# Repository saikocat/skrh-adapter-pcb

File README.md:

# skrh-adapter-pcb
Alps SKRH Switch Adapter PCB

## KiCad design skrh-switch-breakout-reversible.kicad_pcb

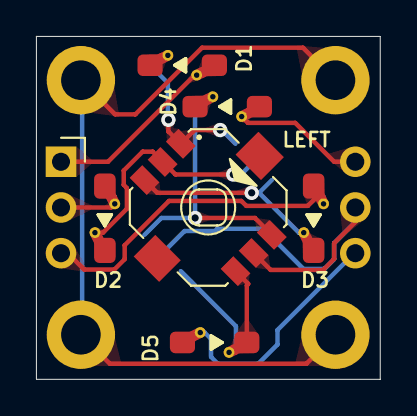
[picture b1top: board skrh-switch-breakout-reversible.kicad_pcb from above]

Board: 2 copper layers, 19.1 x 19.1 mm, 11 parts (0 on the bottom side), 12 nets.

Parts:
D1, D2, D3, D4, D5: 1N4148; Diode_D_SOD-123_Silkless_Reversible
H1, H2, H3, H4: Hole; MountingHole_2.2mm_M2_Pad_3.8mm
S1: SW_MultiDirectional_4DCP_SKRHACE010; SW_MultiDirectional_4DCP_SKRHACE010_SMD_7.5x7.5mm_DualSide
S2: Source; SW_MX_1u_PCB_SKRHAdapter

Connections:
A_SRC: D1.2 (A), S2.1 (A)
A_UP: D1.1 (K), S1.1 (A)
B_RIGHT: D4.1 (K), S1.4 (B)
B_SRC: D4.2 (A), S2.4 (B)
COMMON: S1.5 (COM), S2.5 (COM)
C_LEFT: D3.1 (K), S1.3 (C)
C_SRC: D3.2 (A), S2.3 (C)
D_DOWN: D5.1 (K), S1.6 (D)
D_SRC: D5.2 (A), S2.6 (D)
GND: H1.1, H2.1, H3.1, H4.1
PUSH: D2.1 (K), S1.2 (CENTER)
PUSH_SRC: D2.2 (A), S2.2 (CENTER)

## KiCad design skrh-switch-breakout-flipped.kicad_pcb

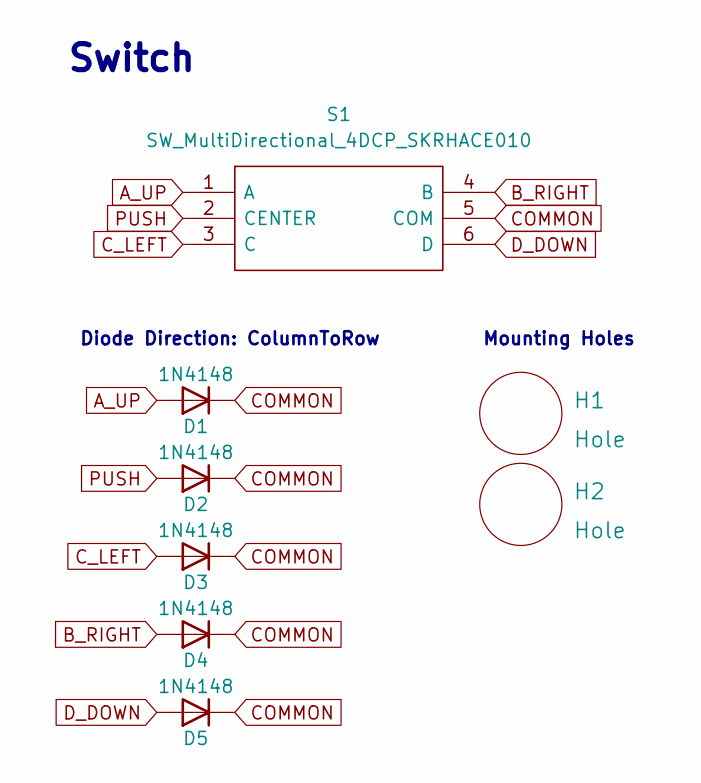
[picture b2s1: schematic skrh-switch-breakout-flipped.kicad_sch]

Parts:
D1, D2, D3, D4, D5: 1N4148; Diode_D_SOD-123_Silkless_Reversible
H1, H2: Hole; MountingHole_2.3mm_M2_Threaded_ISO14580_Pad
S1: SW_MultiDirectional_4DCP_SKRHACE010; SW_MultiDirectional_4DCP_SKRHACE010_SMD_7.5x7.5mm_Breakout_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; Manufacturer_Part_Number SKRHACE010; Mouser Part Number 688-SKRHAC

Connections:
A_UP: D1.2 (A), S1.1 (A)
B_RIGHT: D4.2 (A), S1.4 (B)
COMMON: D1.1 (K), D2.1 (K), D3.1 (K), D4.1 (K), D5.1 (K), S1.5 (COM)
C_LEFT: D3.2 (A), S1.3 (C)
D_DOWN: D5.2 (A), S1.6 (D)
PUSH: D2.2 (A), S1.2 (CENTER)

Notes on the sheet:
Mounting Holes
Switch
Diode Direction: ColumnToRow

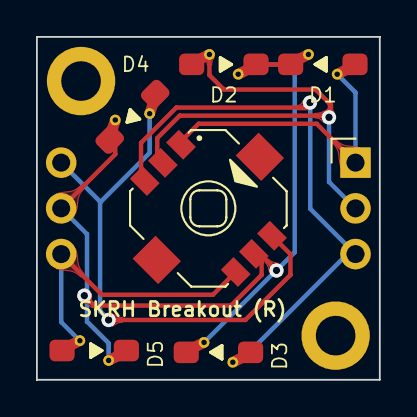
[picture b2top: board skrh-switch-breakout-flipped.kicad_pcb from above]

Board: 2 copper layers, 19.0 x 19.1 mm, 8 parts (0 on the bottom side), 6 nets.

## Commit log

2023-02-03 [setup] add basic repo settings
2023-02-04 [setup] add kicad base
2023-02-05 add breakout for left side
2023-02-05 add breakout for right side
2023-04-02 Add reversible version with correct schematic
2023-04-03 Removed old designs and wrong schematic
